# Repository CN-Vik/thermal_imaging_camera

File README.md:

# thermal_imaging_camera

#### 介绍
红外热成像相机基于ESP32S3

#### 软件架构
软件架构说明

#### 安装教程

1.  xxxx
2.  xxxx
3.  xxxx

#### 使用说明

1.  xxxx
2.  xxxx
3.  xxxx

#### 参与贡献

1.  Fork 本仓库
2.  新建 Feat_xxx 分支
3.  提交代码
4.  新建 Pull Request

#### 特技

1.  使用 Readme\_XXX.md 来支持不同的语言，例如 Readme\_en.md, Readme\_zh.md
2.  Gitee 官方博客 [blog.gitee.com](https://blog.gitee.com)
3.  你可以 [https://gitee.com/explore](https://gitee.com/explore) 这个地址来了解 Gitee 上的优秀开源项目
4.  [GVP](https://gitee.com/gvp) 全称是 Gitee 最有价值开源项目，是综合评定出的优秀开源项目
5.  Gitee 官方提供的使用手册 [https://gitee.com/help](https://gitee.com/help)
6.  Gitee 封面人物是一档用来展示 Gitee 会员风采的栏目 [https://gitee.com/gitee-stars/](https://gitee.com/gitee-stars/)

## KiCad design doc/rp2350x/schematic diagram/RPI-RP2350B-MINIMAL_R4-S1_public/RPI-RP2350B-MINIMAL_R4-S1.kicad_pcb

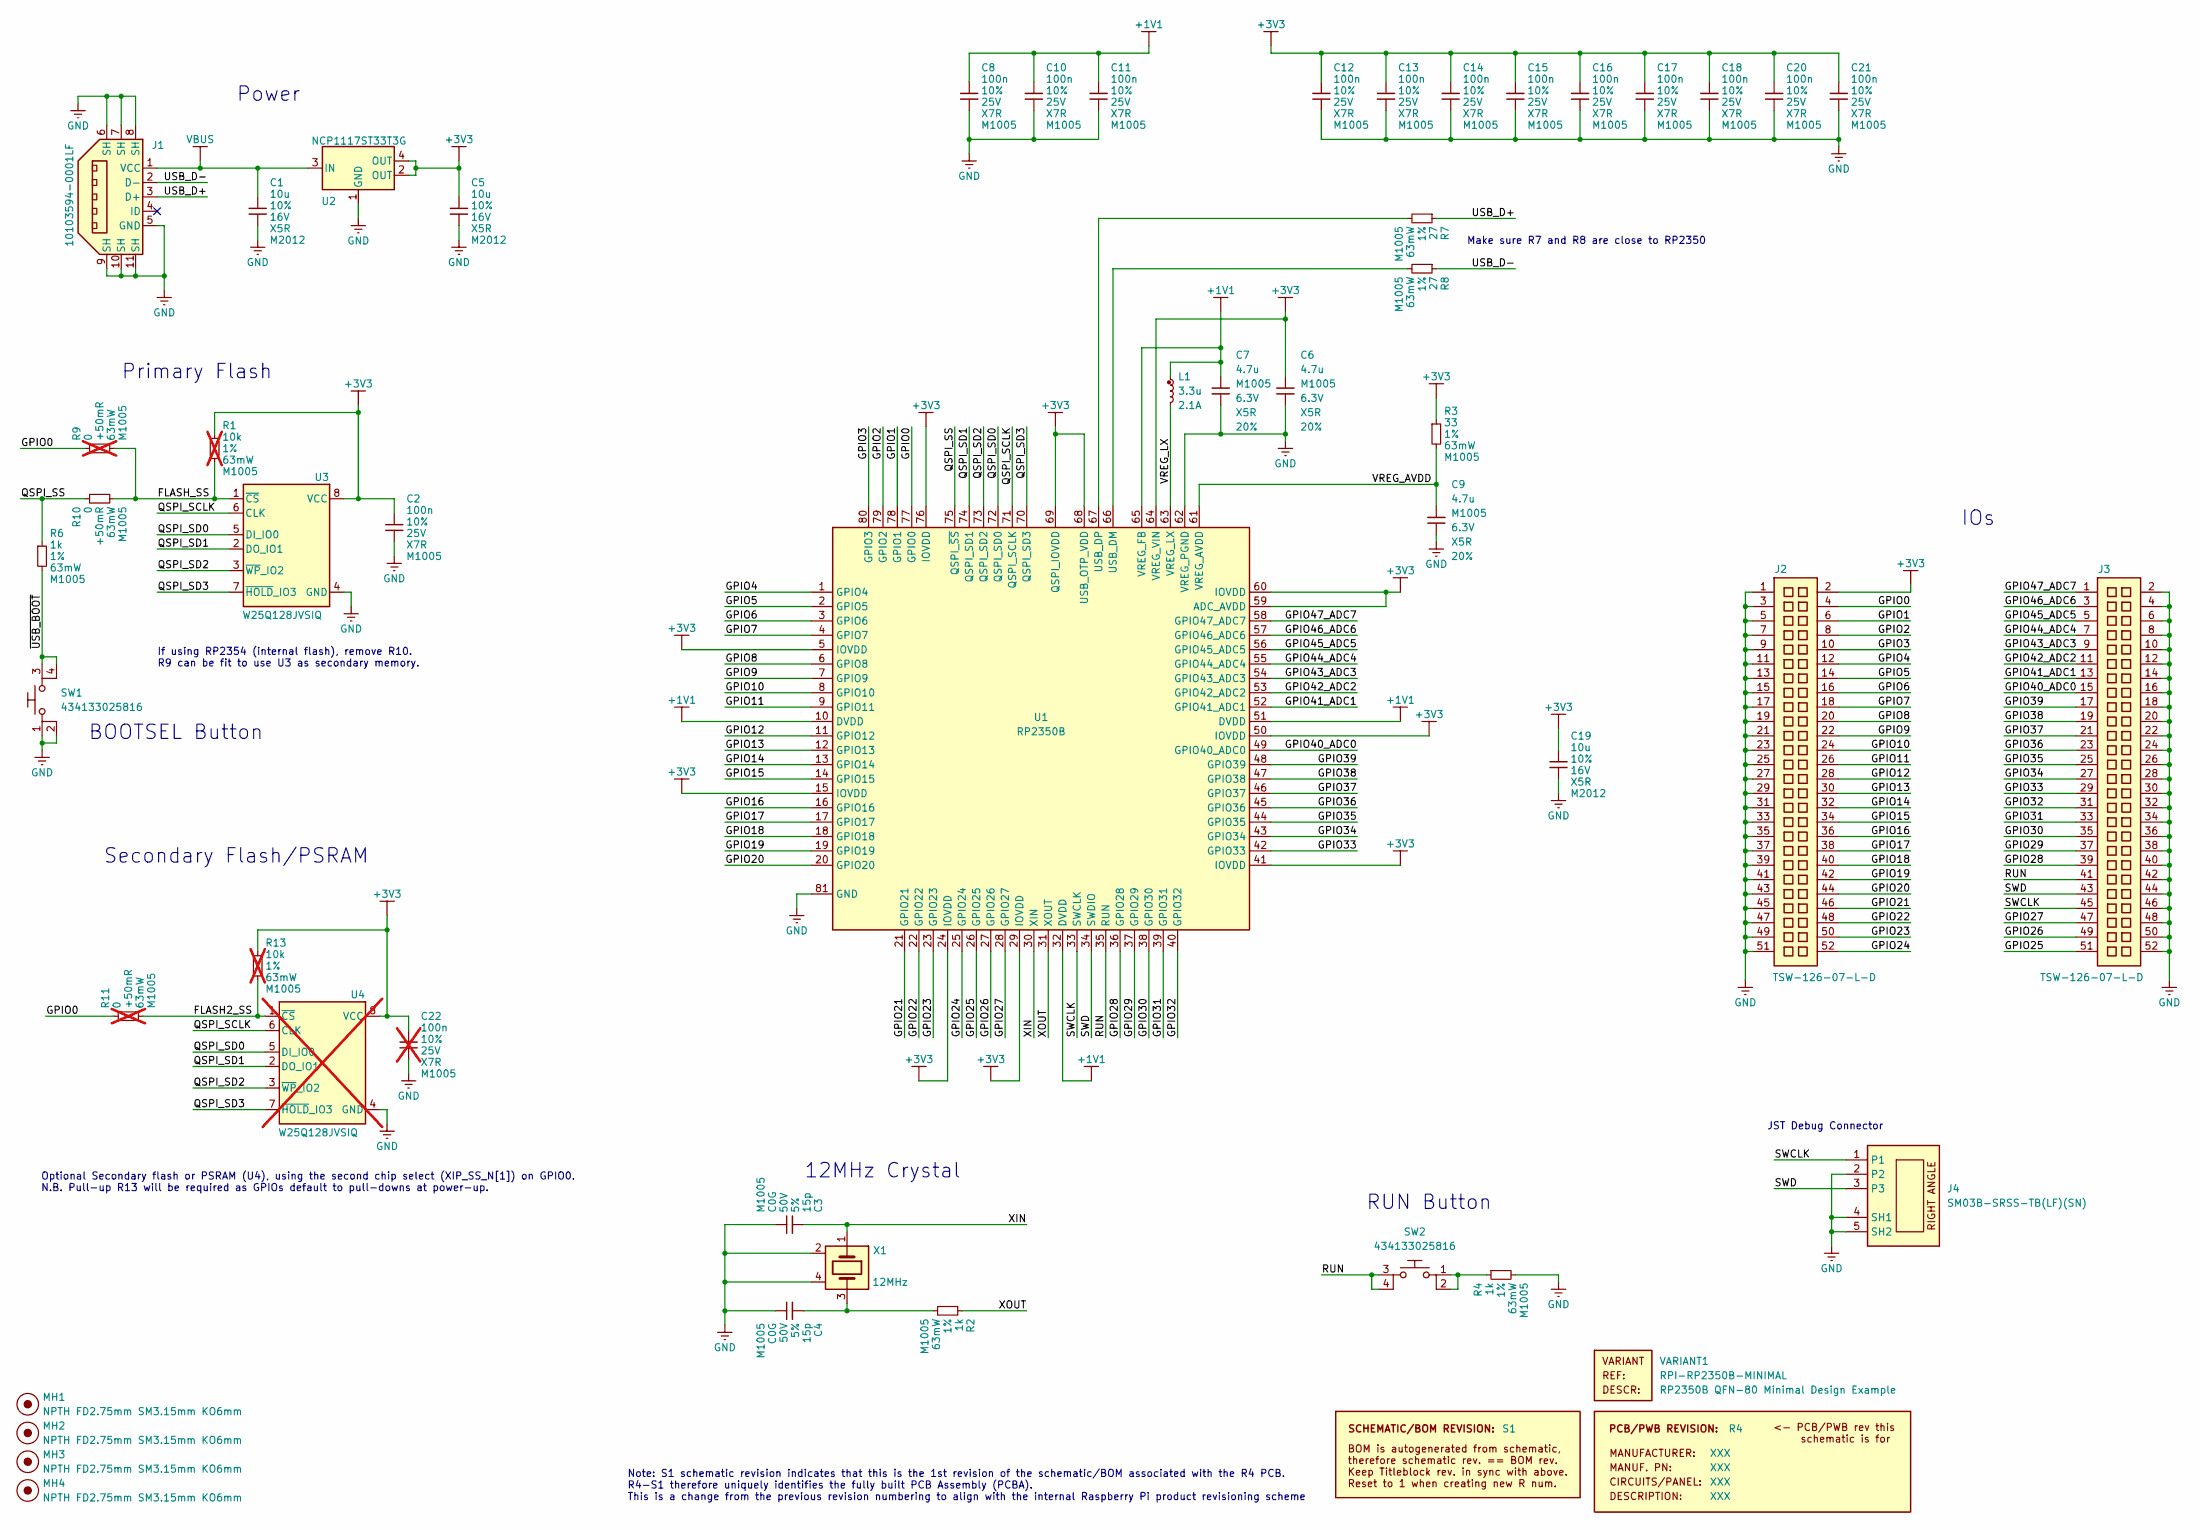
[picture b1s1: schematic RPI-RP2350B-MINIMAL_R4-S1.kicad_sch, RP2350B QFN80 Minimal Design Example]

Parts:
C1, C5, C19: 10u; generic_capc2012x125; voltage 16V; tolerance 10%; part_uid RP-01GYSK-AVBE41
C2, C8, C10, C11, C12, C13, C14, C15, C16, C17, C18, C20, C21: 100n; generic_capc1005x50; voltage 25V; tolerance 10%; part_uid RP-01BJ9Y-KRGF41
C3, C4: 15p; generic_capc1005x50; voltage 50V; tolerance 5%; part_uid RP-01C89W-LLY9XV
C6, C7: 4.7u; generic_capc1005x50_wide; voltage 6.3V; tolerance 20%; part_uid RP-019A1P-0C2GHY
C9: 4.7u; generic_capc1005x50; voltage 6.3V; tolerance 20%; part_uid RP-019A1P-0C2GHY
C22: 100n; generic_capc1005x50; voltage 25V; tolerance 10%; part_uid RP-01BJ9Y-KRGF41; not fitted
J1: 10103594-0001LF; amphenol_10103594-0001lf; part_uid RP-019A1P-1JAX7V
J2, J3: TSW-126-07-L-D; samtec_tsw-126-07-l-d; part_uid RP-01KJ62-FD8Y6K
J4: SM03B-SRSS-TB(LF)(SN); jst_sm03b-srss-tb-lf--sn-; part_uid RP-01EKJ1-8V9SV1
L1: 3.3u; abracon_aota-b201610s3r3-101-t; tolerance 20%; part_uid RP-01GY5D-2VC7WP
MH1, MH2, MH3, MH4: NPTH FD2.75mm SM3.15mm KO6mm; none_mh_npth_fd2p75mm_sm3p15mm_ko6mm; part_uid RP-01HF5R-LCTEJS
PCB1: R4; manufacturer_pn XXX
R1, R13: 10k; generic_resc1005x35; tolerance 1%; voltage 50V; part_uid RP-019A1P-53DHSX; not fitted
R2, R4, R6: 1k; generic_resc1005x35; tolerance 1%; voltage 50V; part_uid RP-019A1P-4Z6ZWY
R3: 33; generic_resc1005x35; tolerance 1%; voltage 50V; part_uid RP-019A1P-58PW9L
R7, R8: 27; generic_resc1005x35; tolerance 1%; voltage 50V; part_uid RP-01C89V-LTEYC4
R9, R11: 0; generic_resc1005x35; tolerance +50mR; voltage 50V; part_uid RP-019A1P-4Y4V63; not fitted
R10: 0; generic_resc1005x35; tolerance +50mR; voltage 50V; part_uid RP-019A1P-4Y4V63
SBREV1: S1
SW1, SW2: 434133025816; wurthelek_434133025816; part_uid RP-01H0MT-6E9H8F
U1: RP2350B; rpi_rp2350b_vias; part_uid RP-01HA9H-ABBLJN
U2: NCP1117ST33T3G; onsemi_ncp1117st33t3g; voltage 3.3V; part_uid RP-01JWD9-7JRX6J
U3: W25Q128JVSIQ; generic_soic127p790x195-8; voltage 2.7-3.6V; part_uid RP-01JWD4-F1H4N9
U4: W25Q128JVSIQ; generic_soic127p790x195-8; voltage 2.7-3.6V; part_uid RP-01JWD4-F1H4N9; not fitted
VARIANT1: RPI-RP2350B-MINIMAL
X1: 12MHz; generic_xtalcc320x250x80-4; tolerance 30ppm; part_uid RP-01G8X7-GS352B

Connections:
+1V1: C7.1, C8.1, C10.1, C11.1, L1.1, U1.10 (DVDD), U1.32 (DVDD), U1.51 (DVDD), U1.65 (VREG_FB)
+3V3: C2.1, C5.1, C6.1, C12.1, C13.1, C14.1, C15.1, C16.1, C17.1, C18.1, C19.1, C20.1, C21.1, C22.1, J2.2, R1.1, R3.1, R13.1, U1.5 (IOVDD), U1.15 (IOVDD), U1.24 (IOVDD), U1.29 (IOVDD), U1.41 (IOVDD), U1.50 (IOVDD), U1.59 (ADC_AVDD), U1.60 (IOVDD), U1.64 (VREG_VIN), U1.68 (USB_OTP_VDD), U1.69 (QSPI_IOVDD), U1.76 (IOVDD), U2.2 (OUT), U2.4 (OUT), U3.8 (VCC), U4.8 (VCC)
/FLASH2_SS: R11.2, R13.2, U4.1 (~CS)
/FLASH_SS: R1.2, R9.2, R10.2, U3.1 (~CS)
/GPIO0: J2.4, R9.1, R11.1, U1.77 (GPIO0)
/GPIO1: J2.6, U1.78 (GPIO1)
/GPIO2: J2.8, U1.79 (GPIO2)
/GPIO3: J2.10, U1.80 (GPIO3)
/GPIO4: J2.12, U1.1 (GPIO4)
/GPIO5: J2.14, U1.2 (GPIO5)
/GPIO6: J2.16, U1.3 (GPIO6)
/GPIO7: J2.18, U1.4 (GPIO7)
/GPIO8: J2.20, U1.6 (GPIO8)
/GPIO9: J2.22, U1.7 (GPIO9)
/GPIO10: J2.24, U1.8 (GPIO10)
/GPIO11: J2.26, U1.9 (GPIO11)
/GPIO12: J2.28, U1.11 (GPIO12)
/GPIO13: J2.30, U1.12 (GPIO13)
/GPIO14: J2.32, U1.13 (GPIO14)
/GPIO15: J2.34, U1.14 (GPIO15)
/GPIO16: J2.36, U1.16 (GPIO16)
/GPIO17: J2.38, U1.17 (GPIO17)
/GPIO18: J2.40, U1.18 (GPIO18)
/GPIO19: J2.42, U1.19 (GPIO19)
/GPIO20: J2.44, U1.20 (GPIO20)
/GPIO21: J2.46, U1.21 (GPIO21)
/GPIO22: J2.48, U1.22 (GPIO22)
/GPIO23: J2.50, U1.23 (GPIO23)
/GPIO24: J2.52, U1.25 (GPIO24)
/GPIO25: J3.51, U1.26 (GPIO25)
/GPIO26: J3.49, U1.27 (GPIO26)
/GPIO27: J3.47, U1.28 (GPIO27)
/GPIO28: J3.39, U1.36 (GPIO28)
/GPIO29: J3.37, U1.37 (GPIO29)
/GPIO30: J3.35, U1.38 (GPIO30)
/GPIO31: J3.33, U1.39 (GPIO31)
/GPIO32: J3.31, U1.40 (GPIO32)
/GPIO33: J3.29, U1.42 (GPIO33)
/GPIO34: J3.27, U1.43 (GPIO34)
/GPIO35: J3.25, U1.44 (GPIO35)
/GPIO36: J3.23, U1.45 (GPIO36)
/GPIO37: J3.21, U1.46 (GPIO37)
/GPIO38: J3.19, U1.47 (GPIO38)
/GPIO39: J3.17, U1.48 (GPIO39)
/GPIO40_ADC0: J3.15, U1.49 (GPIO40_ADC0)
/GPIO41_ADC1: J3.13, U1.52 (GPIO41_ADC1)
/GPIO42_ADC2: J3.11, U1.53 (GPIO42_ADC2)
/GPIO43_ADC3: J3.9, U1.54 (GPIO43_ADC3)
/GPIO44_ADC4: J3.7, U1.55 (GPIO44_ADC4)
/GPIO45_ADC5: J3.5, U1.56 (GPIO45_ADC5)
/GPIO46_ADC6: J3.3, U1.57 (GPIO46_ADC6)
/GPIO47_ADC7: J3.1, U1.58 (GPIO47_ADC7)
/QSPI_SCLK: U1.71 (QSPI_SCLK), U3.6 (CLK), U4.6 (CLK)
/QSPI_SD0: U1.72 (QSPI_SD0), U3.5 (DI_IO0), U4.5 (DI_IO0)
/QSPI_SD1: U1.74 (QSPI_SD1), U3.2 (DO_IO1), U4.2 (DO_IO1)
/QSPI_SD2: U1.73 (QSPI_SD2), U3.3 (~WP_IO2), U4.3 (~WP_IO2)
/QSPI_SD3: U1.70 (QSPI_SD3), U3.7 (~HOLD_IO3), U4.7 (~HOLD_IO3)
/QSPI_SS: R6.1, R10.1, U1.75 (QSPI_~SS)
/RUN: J3.41, SW2.3, SW2.4, U1.35 (RUN)
/SWCLK: J3.45, J4.1, U1.33 (SWCLK)
/SWD: J3.43, J4.3, U1.34 (SWDIO)
/USB_D+: J1.3 (D+), R7.1
/USB_D-: J1.2 (D-), R8.1
/VREG_AVDD: C9.1, R3.2, U1.61 (VREG_AVDD)
/VREG_LX: L1.2, U1.63 (VREG_LX)
/XIN: C3.1, U1.30 (XIN), X1.1
/XOUT: R2.1, U1.31 (XOUT)
/~USB_BOOT: R6.2, SW1.3, SW1.4
GND: C1.2, C2.2, C3.2, C4.2, C5.2, C6.2, C7.2, C8.2, C9.2, C10.2, C11.2, C12.2, C13.2, C14.2, C15.2, C16.2, C17.2, C18.2, C19.2, C20.2, C21.2, C22.2, J1.5 (GND), J1.6 (SH), J1.7 (SH), J1.8 (SH), J1.9 (SH), J1.10 (SH), J1.11 (SH), J2.1, J2.3, J2.5, J2.7, J2.9, J2.11, J2.13, J2.15, J2.17, J2.19, J2.21, J2.23, J2.25, J2.27, J2.29, J2.31, J2.33, J2.35, J2.37, J2.39, J2.41, J2.43, J2.45, J2.47, J2.49, J2.51, J3.2, J3.4, J3.6, J3.8, J3.10, J3.12, J3.14, J3.16, J3.18, J3.20, J3.22, J3.24, J3.26, J3.28, J3.30, J3.32, J3.34, J3.36, J3.38, J3.40, J3.42, J3.44, J3.46, J3.48, J3.50, J3.52, J4.2, J4.4 (SH1), J4.5 (SH2), R4.2, SW1.1, SW1.2, U1.62 (VREG_PGND), U1.81 (GND), U2.1 (GND), U3.4 (GND), U4.4 (GND), X1.2, X1.4
unnamed: C4.1, R2.2, X1.3
unnamed: R4.1, SW2.1, SW2.2
unnamed: R8.2, U1.66 (USB_DM)
unnamed: R7.2, U1.67 (USB_DP)
VBUS: C1.1, J1.1 (VCC), U2.3 (IN)

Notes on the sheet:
Optional Secondary flash or PSRAM (U4), using the second chip select (XIP_SS_N[1]) on GPIO0. N.B. Pull-up R13 will be required as GPIOs default to pull-downs at power-up.
IOs
If using RP2354 (internal flash), remove R10. R9 can be fit to use U3 as secondary memory.
Note: S1 schematic revision indicates that this is the 1st revision of the schematic/BOM associated with the R4 PCB. R4-S1 therefore uniquely identifies the fully built PCB Assembly (PCBA). This is a change from the previous revision numbering to align with the internal Raspberry Pi product revisio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
RUN Button
Primary Flash
BOOTSEL Button
JST Debug Connector
12MHz Crystal
Make sure R7 and R8 are close to RP2350
Secondary Flash/PSRAM
Power

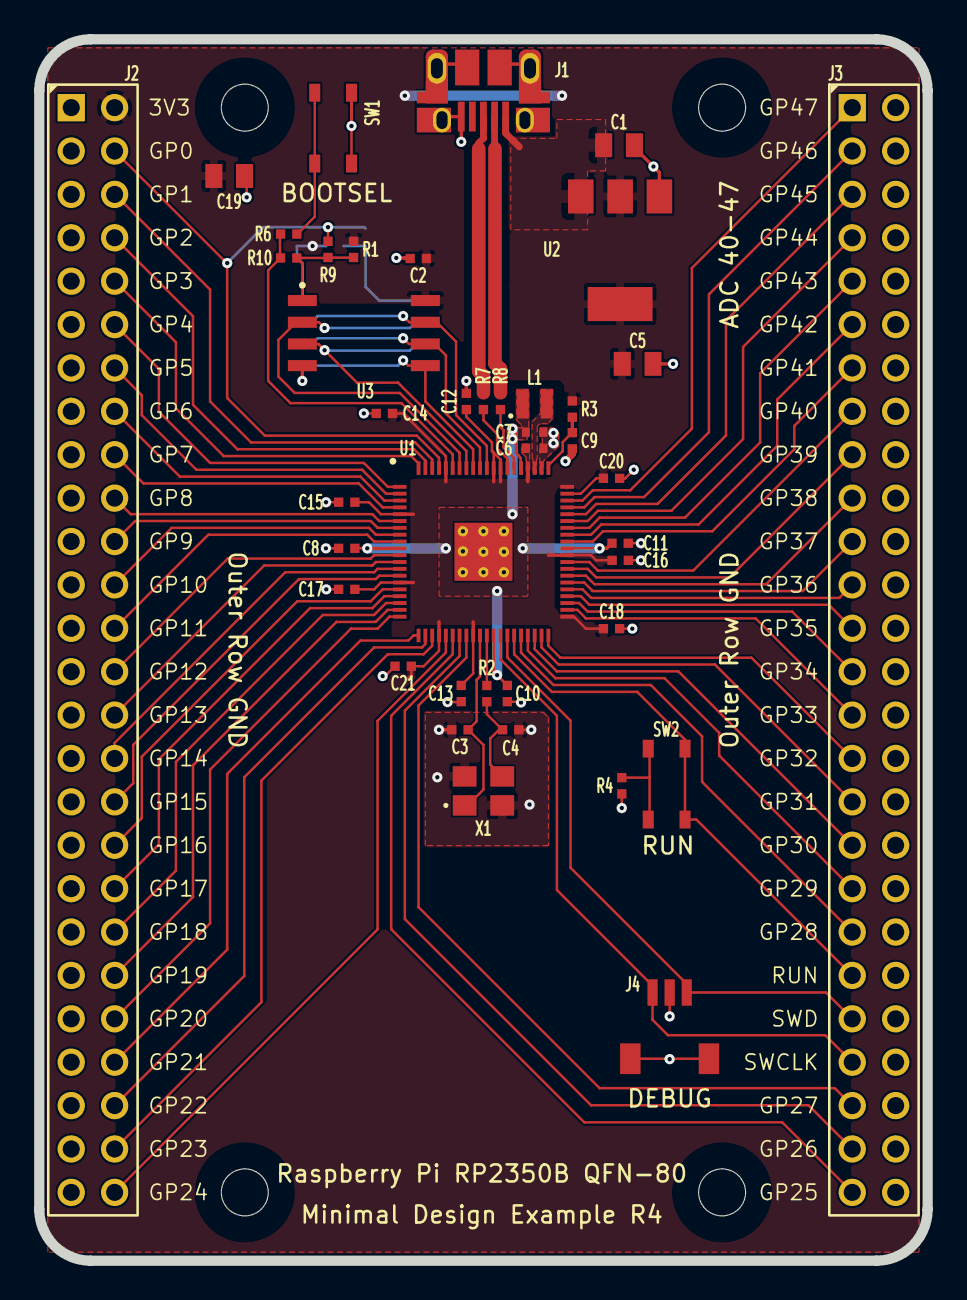
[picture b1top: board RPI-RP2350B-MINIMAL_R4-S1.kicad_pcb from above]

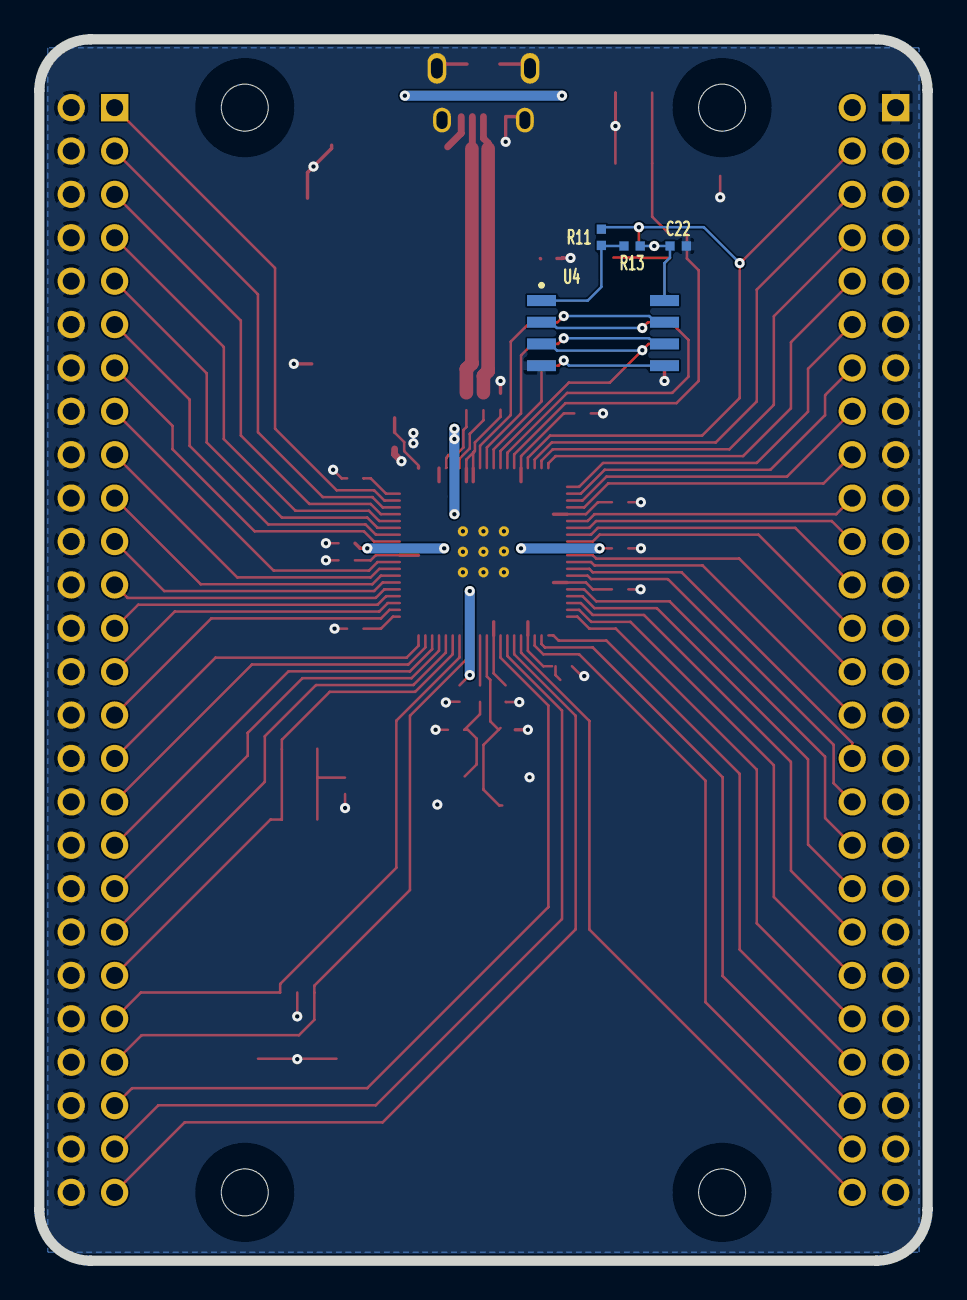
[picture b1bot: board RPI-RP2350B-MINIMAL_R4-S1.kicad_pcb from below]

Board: 2 copper layers, 52.0 x 71.5 mm, 49 parts (4 on the bottom side), 74 nets.
